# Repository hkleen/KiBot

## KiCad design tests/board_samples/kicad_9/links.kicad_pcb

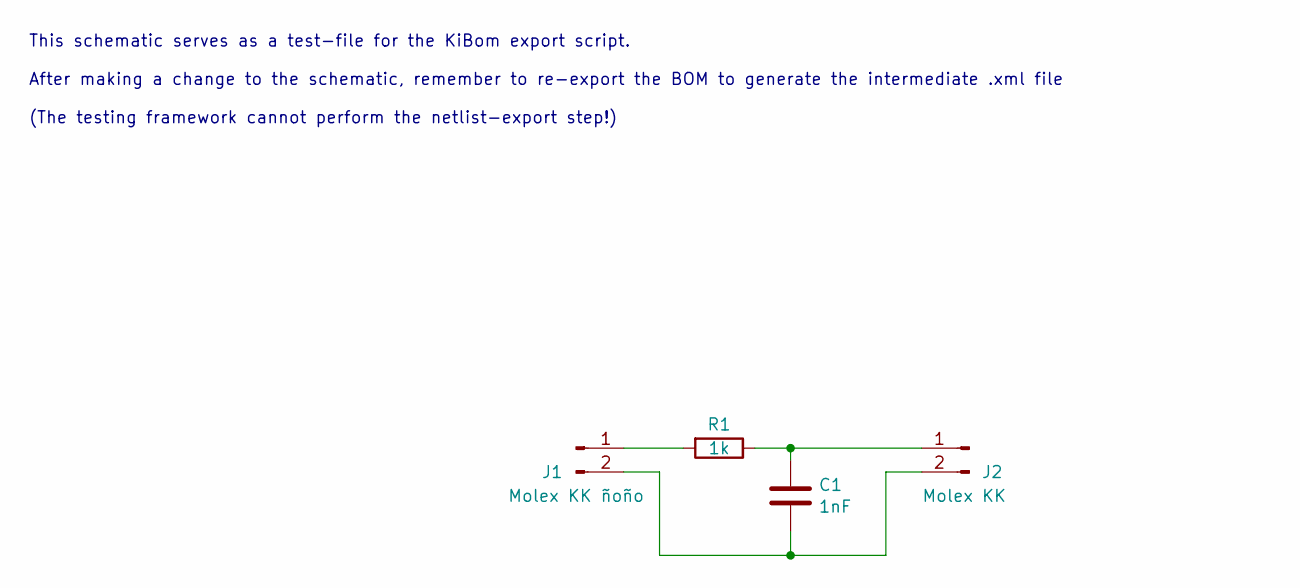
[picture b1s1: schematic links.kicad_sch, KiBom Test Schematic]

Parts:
C1: 1nF; C_0805_2012Metric; mouser# 80-C0805C102K5R; digikey# 399-1147-1-ND
J1: Molex KK ñoño; PinHeader_1x02_P2.54mm_Vertical; mouser# 538-22-23-2021; digikey# 900-0022232021-ND
J2: Molex KK; PinHeader_1x02_P2.54mm_Vertical; mouser# 538-22-23-2021; digikey# 900-0022232021-ND
R1: 1k; R_0805_2012Metric; mouser# 652-CR0805JW-102ELF; digikey# CR0805-JW-102ELFCT-ND

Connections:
unnamed: C1.1, J2.1, R1.1
unnamed: C1.2, J1.2, J2.2
unnamed: J1.1, R1.2

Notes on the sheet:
This schematic serves as a test-file for the KiBom export script. After making a change to the schematic, remember to re-export the BOM to generate the intermediate .xml file (The testing framework cannot perform the netlist-export step!)

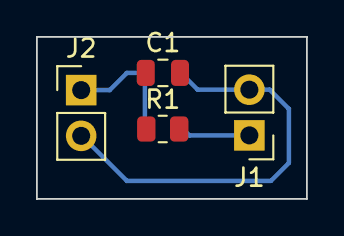
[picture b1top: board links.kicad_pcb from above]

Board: 2 copper layers, 15.0 x 9.0 mm, 4 parts (0 on the bottom side), 3 nets.

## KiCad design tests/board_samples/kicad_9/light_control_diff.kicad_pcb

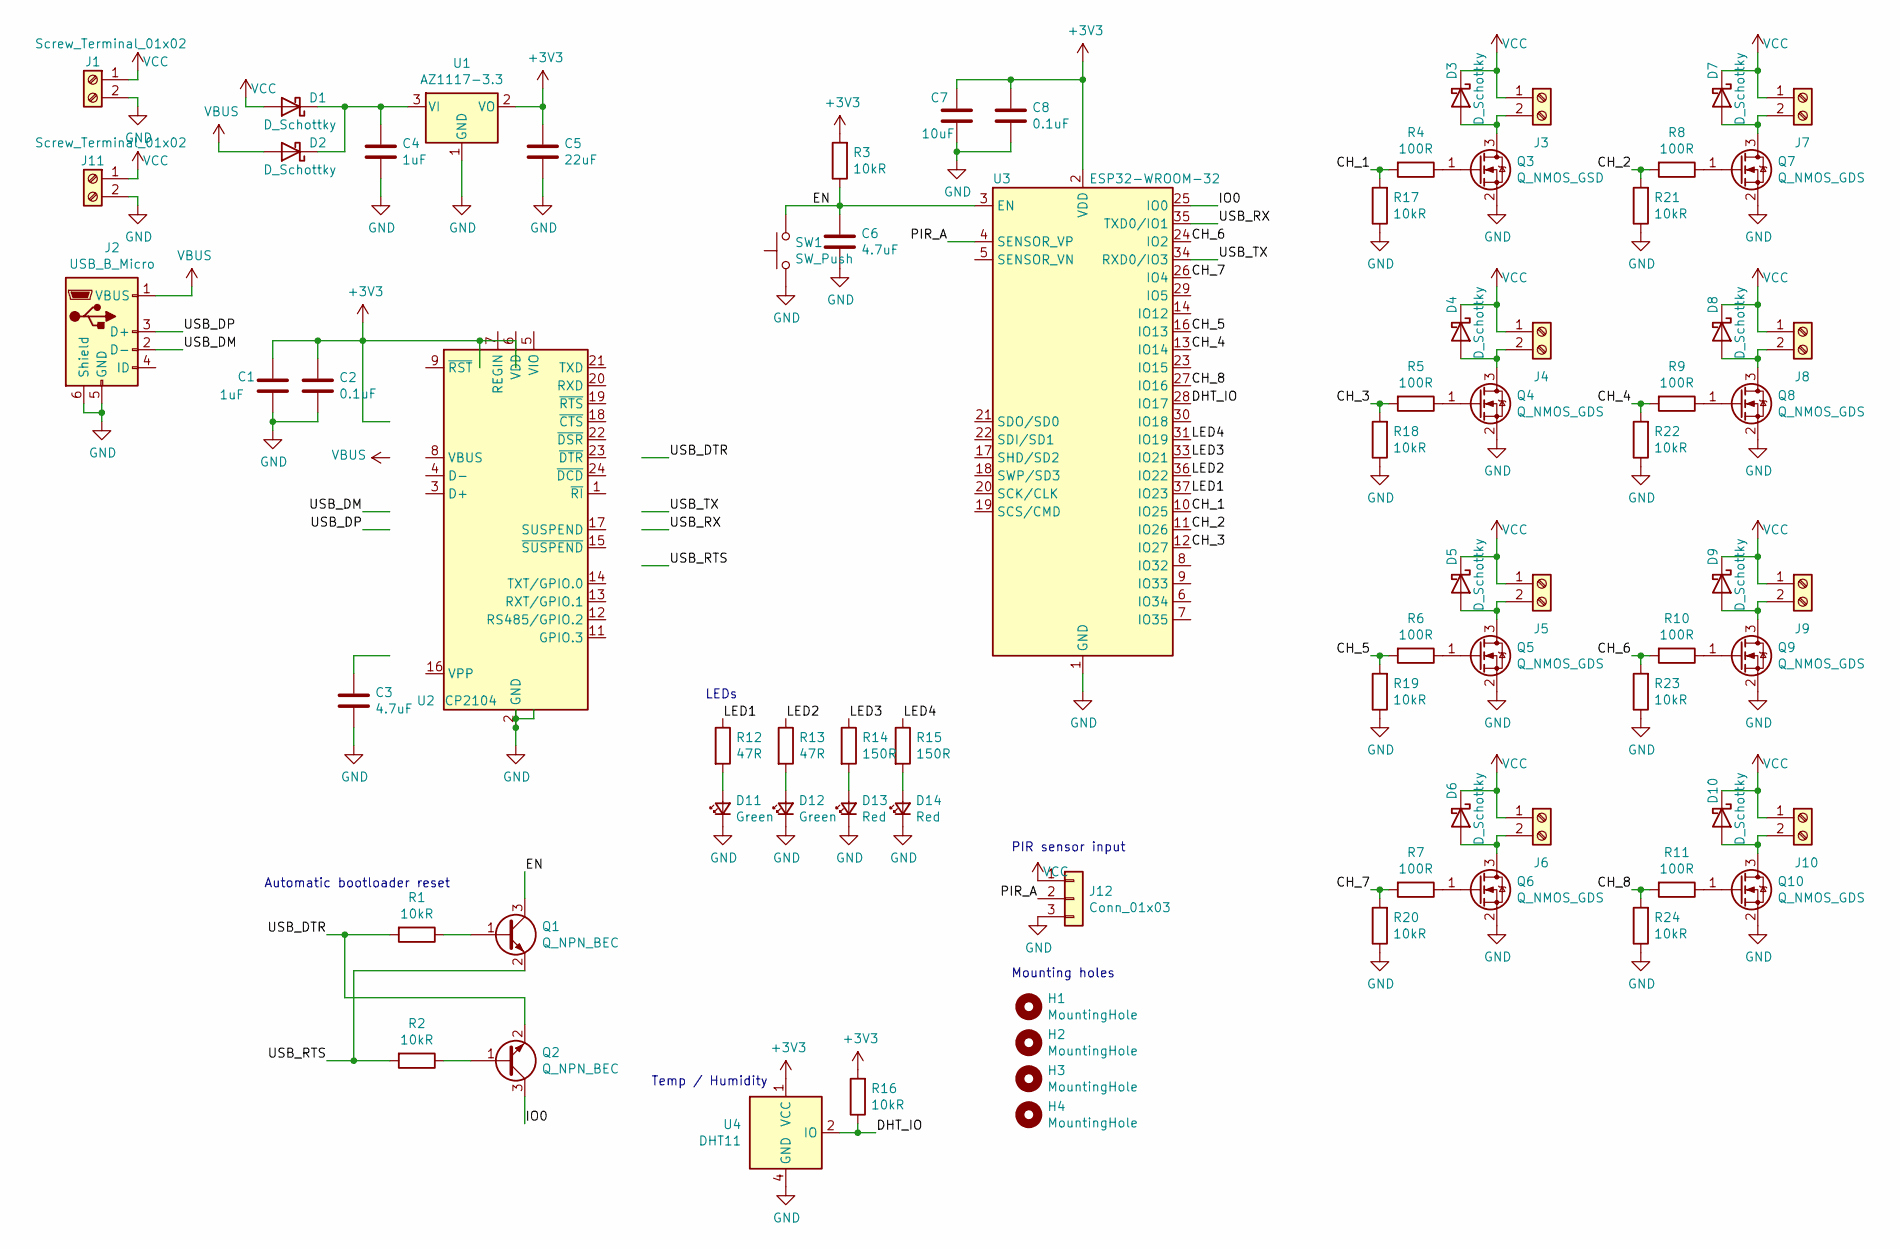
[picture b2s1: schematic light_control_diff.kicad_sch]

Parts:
C1: 1uF; R_0402_1005Metric; MPN CL05A105KA5NQNC; LCSC# C52923
C2, C8: 0.1uF; R_0402_1005Metric; MPN CL05B104KO5NNNC; LCSC# C1525
C3: 4.7uF; R_0603_1608Metric; MPN CL10A475KO8NNNC; LCSC# C19666
C4: 1uF; R_0603_1608Metric; MPN CL10A105KB8NNNC; LCSC# C15849
C5: 22uF; R_0603_1608Metric; MPN CL10A226MQ8NRNC; LCSC# C59461
C6: 4.7uF; R_0402_1005Metric; MPN CL05A475MP5NRNC; LCSC# C23733
C7: 10uF; R_0402_1005Metric; MPN CL05A106MQ5NUNC; LCSC# C15525
D1, D2, D3, D4, D5, D6, D7, D8, D9, D10: D_Schottky; D_SOD-123; MPN B5819W SL; LCSC# C8598
D11, D12: Green; LED_0603_1608Metric; MPN 19-217/GHC-YR1S2/3T; LCSC# C72043
D13, D14: Red; LED_0603_1608Metric; LCSC# C2286
H1, H2, H3, H4: MountingHole; MountingHole_3.2mm_M3
J1, J3, J4, J5, J6, J7, J8, J9, J10, J11: Screw_Terminal_01x02; TerminalBlock_Phoenix_PT-1,5-2-3.5-H_1x02_P3.50mm_Horizontal
J2: USB_B_Micro; USB_Micro-B_Molex-105017-0001
J12: Conn_01x03; JST_XH_B3B-XH-A_1x03_P2.50mm_Vertical
Q1, Q2: Q_NPN_BEC; SOT-23; MPN SS8050; LCSC# C2150
Q3: Q_NMOS_GSD; SOT-23; MPN AO3400A; LCSC# C20917
Q4, Q5, Q6, Q7, Q8, Q9, Q10: Q_NMOS_GDS; SOT-23; MPN AO3400A; LCSC# C20917
R1, R2, R3, R16, R17, R18, R19, R20, R21, R22, R23, R24: 10kR; R_0402_1005Metric; MPN 0402WGF1002TCE; LCSC# C25744
R4, R5, R6, R7, R8, R9, R10, R11: 100R; R_0402_1005Metric; MPN 0402WGF1000TCE; LCSC# C25076
R12: 47R; R_0402_1005Metric; MPN 19-217/GHC-YR1S2/3T; LCSC# C25118
R13: 47R; R_0402_1005Metric; MPN 0402WGF470JTCE; LCSC# C25118
R14, R15: 150R; R_0402_1005Metric; MPN 0402WGF1500TCE; LCSC# C25082
SW1: SW_Push; TS-1187A; MPN TS-1187A-C-D-B; LCSC# C318888
U1: AZ1117-3.3; SOT-223-3_TabPin2; MPN AZ1117CH-3.3TRG1; LCSC# C92102
U2: CP2104; QFN-24-1EP_4x4mm_P0.5mm_EP2.6x2.6mm; MPN CP2104-F03-GMR; LCSC# C47742
U3: ESP32-WROOM-32
U4: DHT11; Aosong_DHT11_5.5x12.0_P2.54mm

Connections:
+3V3: C1.1, C2.1, C5.1, C7.1, C8.1, R3.2, R16.2, U1.2 (VO), U2.5 (VIO), U2.6 (VDD), U2.7 (REGIN), U3.2 (VDD), U4.1 (VCC)
/CH_1: R4.2, R17.2, U3.10 (IO25)
/CH_2: R8.2, R21.2, U3.11 (IO26)
/CH_3: R5.2, R18.2, U3.12 (IO27)
/CH_4: R9.2, R22.2, U3.13 (IO14)
/CH_5: R6.2, R19.2, U3.16 (IO13)
/CH_6: R10.2, R23.2, U3.24 (IO2)
/CH_7: R7.2, R20.2, U3.26 (IO4)
/CH_8: R11.2, R24.2, U3.27 (IO16)
/DHT_IO: R16.1, U3.28 (IO17), U4.2 (IO)
/EN: C6.1, Q1.3 (C), R3.1, SW1.2, U3.3 (EN)
/IO0: Q2.3 (C), U3.25 (IO0)
/LED1: R12.1, U3.37 (IO23)
/LED2: R13.1, U3.36 (IO22)
/LED3: R14.1, U3.33 (IO21)
/LED4: R15.1, U3.31 (IO19)
/PIR_A: J12.2, U3.4 (SENSOR_VP)
/USB_DM: J2.2 (D-), U2.4 (D-)
/USB_DP: J2.3 (D+), U2.3 (D+)
/USB_DTR: Q2.2 (E), R1.2, U2.23 (~DTR)
/USB_RTS: Q1.2 (E), R2.2, U2.19 (~RTS)
/USB_RX: U2.20 (RXD), U3.35 (TXD0/IO1)
/USB_TX: U2.21 (TXD), U3.34 (RXD0/IO3)
GND: C1.2, C2.2, C3.2, C4.2, C5.2, C6.2, C7.2, C8.2, D11.1 (K), D12.1 (K), D13.1 (K), D14.1 (K), J1.2, J2.5 (GND), J2.6 (Shield), J11.2, J12.3, Q3.2 (S), Q4.2 (S), Q5.2 (S), Q6.2 (S), Q7.2 (S), Q8.2 (S), Q9.2 (S), Q10.2 (S), R17.1, R18.1, R19.1, R20.1, R21.1, R22.1, R23.1, R24.1, SW1.1, U1.1 (GND), U2.2 (GND), U2.25 (GND), U3.1 (GND), U3.15 (GND), U3.38 (GND), U3.39 (GND), U4.4 (GND)
unnamed: C3.1, U2.16 (VPP)
unnamed: C4.1, D1.1 (K), D2.1 (K), U1.3 (VI)
unnamed: D3.2 (A), J3.2, Q3.3 (D)
unnamed: D4.2 (A), J4.2, Q4.3 (D)
unnamed: D5.2 (A), J5.2, Q5.3 (D)
unnamed: D6.2 (A), J6.2, Q6.3 (D)
unnamed: D7.2 (A), J7.2, Q7.3 (D)
unnamed: D8.2 (A), J8.2, Q8.3 (D)
unnamed: D9.2 (A), J9.2, Q9.3 (D)
unnamed: D10.2 (A), J10.2, Q10.3 (D)
unnamed: D11.2 (A), R12.2
unnamed: D12.2 (A), R13.2
unnamed: D13.2 (A), R14.2
unnamed: D14.2 (A), R15.2
unnamed: Q1.1 (B), R1.1
unnamed: Q2.1 (B), R2.1
unnamed: Q3.1 (G), R4.1
unnamed: Q4.1 (G), R5.1
unnamed: Q5.1 (G), R6.1
unnamed: Q6.1 (G), R7.1
unnamed: Q7.1 (G), R8.1
unnamed: Q8.1 (G), R9.1
unnamed: Q9.1 (G), R10.1
unnamed: Q10.1 (G), R11.1
VBUS: D2.2 (A), J2.1 (VBUS), U2.8 (VBUS)
VCC: D1.2 (A), D3.1 (K), D4.1 (K), D5.1 (K), D6.1 (K), D7.1 (K), D8.1 (K), D9.1 (K), D10.1 (K), J1.1, J3.1, J4.1, J5.1, J6.1, J7.1, J8.1, J9.1, J10.1, J11.1, J12.1

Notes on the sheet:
PIR sensor input
Mounting holes
Temp / Humidity
LEDs
Automatic bootloader reset

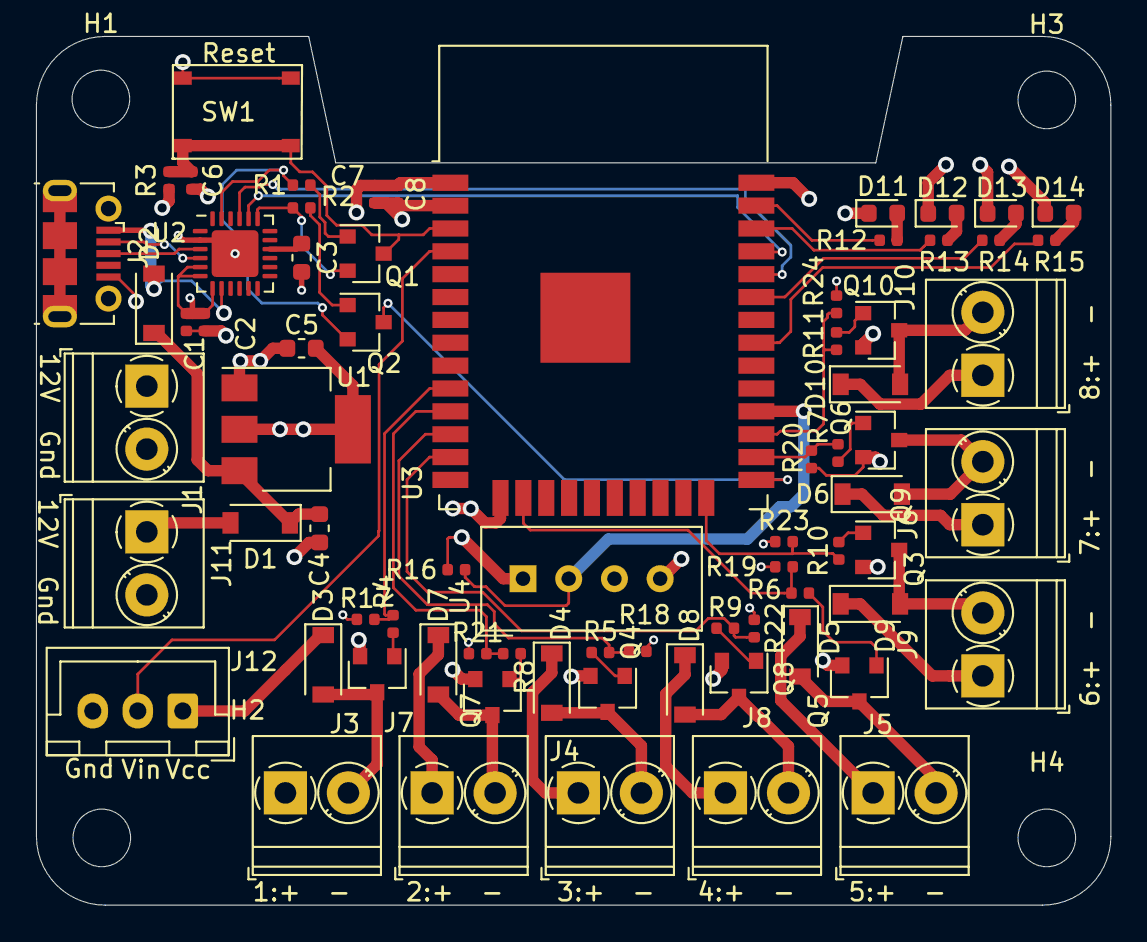
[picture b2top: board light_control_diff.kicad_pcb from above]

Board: 4 copper layers, 59.7 x 48.3 mm, 77 parts (0 on the bottom side), 50 nets.

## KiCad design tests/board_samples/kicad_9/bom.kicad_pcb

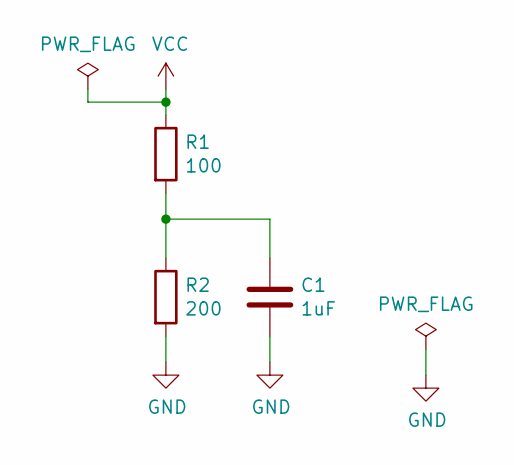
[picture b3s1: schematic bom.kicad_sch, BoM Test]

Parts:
C1: 1uF; C_0805_2012Metric
R1: 100; R_0805_2012Metric
R2: 200; R_0805_2012Metric

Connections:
GND: C1.2, R2.2
unnamed: C1.1, R1.2, R2.1
VCC: R1.1

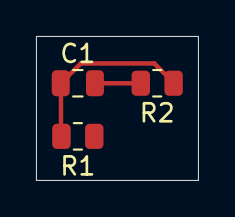
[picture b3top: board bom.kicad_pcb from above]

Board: 2 copper layers, 9.0 x 8.0 mm, 3 parts (0 on the bottom side), 2 nets.

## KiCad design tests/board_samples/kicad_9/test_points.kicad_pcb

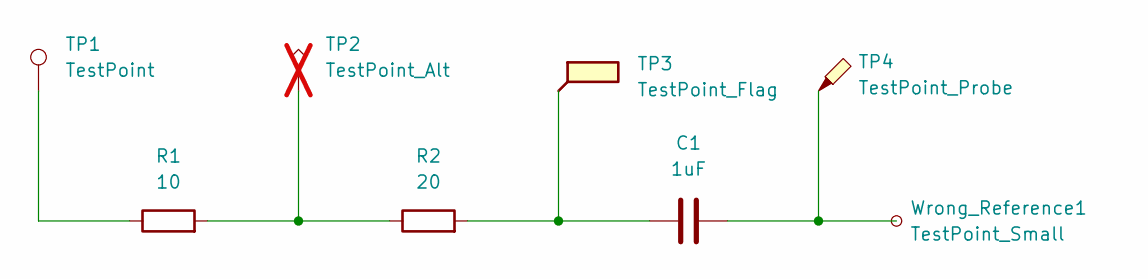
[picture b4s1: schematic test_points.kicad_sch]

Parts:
C1: 1uF; C_0805_2012Metric
R1: 10; R_0805_2012Metric
R2: 20; R_0805_2012Metric
TP1: TestPoint; TestPoint_Loop_D1.80mm_Drill1.0mm_Beaded
TP2: TestPoint_Alt; TestPoint_Pad_1.0x1.0mm; not fitted
TP3: TestPoint_Flag; TestPoint_Plated_Hole_D2.0mm
TP4: TestPoint_Probe; TestPoint_Pad_D2.0mm
Wrong_Reference1: TestPoint_Small; TestPoint_Pad_D1.0mm

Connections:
unnamed: C1.1, R2.2, TP3.1
unnamed: C1.2, TP4.1, Wrong_Reference1.1
unnamed: R1.1, TP1.1
unnamed: R1.2, R2.1, TP2.1

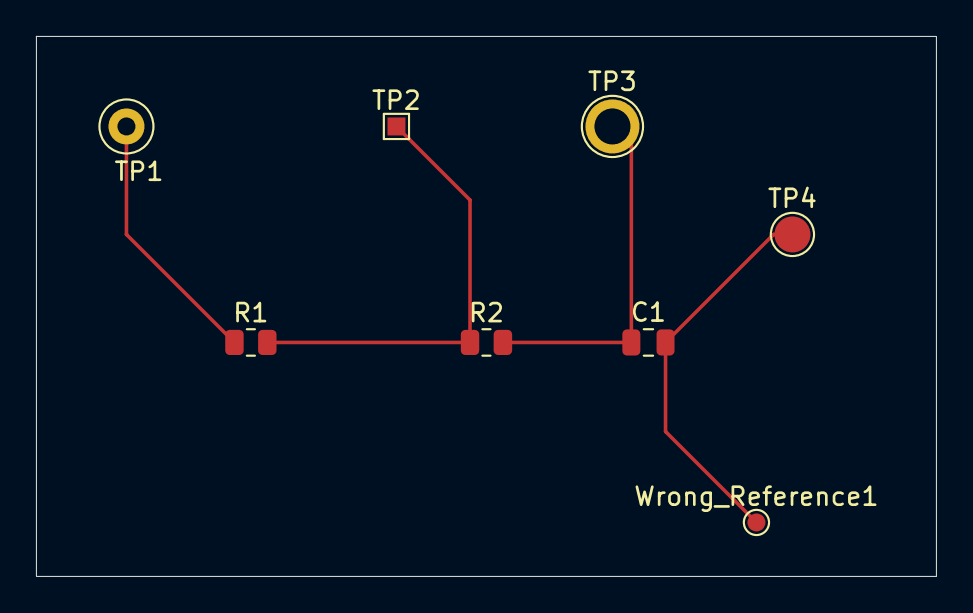
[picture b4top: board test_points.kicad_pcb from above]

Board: 2 copper layers, 50.0 x 30.0 mm, 8 parts (0 on the bottom side), 4 nets.

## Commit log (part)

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2022-03-21 Switched to KiCost/master
2022-04-11 Test to add configurable title block to pcb_print
    - Doesn't work, KiCad can't load the wks from Python, just the default.
2024-05-17 fix indentation
2024-10-29 [PCB Print][Fixed] Problems with the forced edge
    Introduced by the patch that implements #706
2024-10-29 [Debian][Fixed] Missing tools in resources
2024-10-29 [Test][GUI][Preflights] Force to select the dict versions
    When we have boolean + dict
2024-10-30 [BoM][Added] KiCad internal BoM special fields
    At least all the ones I found, trying to make them to behave like in KiCad
2024-10-30 [BoM][Added] Mechanism to import fields from KiCad's BoM
    - You can import the fields and the grouping
    - Also added a new option "group_not_fitted" to mimic KiCad behavior
2024-10-31 [BoM][Added] Range separator configuration
    - `ref_range_separator`
    - Also `use_ref_ranges` alias for `use_alt`
2024-11-01 [PCB Print][Fixed] Groups are KiCad 6+ feature
2024-11-01 [DOCs][BoM][Added] Notes about things not imported from KiCad
    - DNP ex/inclusion, controlled by global `kicad_dnp_applied`
    - String filter, controlled by filters
2024-11-01 [PcbDraw][Changed] SVG size when no contour
    Was 0x0 mm, now is A4 landscape
2024-11-11 Revert "[Changed] Try to use "Rescue" layer again"
    This reverts commit a3e99c178006ccb117bf469e6b556d4d0a483bd2.
2024-11-12 [Fixed] Some times we don't initialize the global options
    So we don't need to check if the global work layer is valid all the time
2024-11-12 [Fixed] The image replacer needs KiCad 6+
    See #713
2024-11-13 [Fix] Handle no matching key for out_to_csv_mapping
2024-11-14 [DOCs][Drill] Updated
    - Also added a warning when generating nothing
    - Also removed redundant option in excellon (from any)
2024-11-14 [Added] Stronger workaround for people using backslashes in WKSs
    Should cover all the cases where we read the WKSs from the project
    See #719 and #607
2024-11-20 [Feature] Support OTF fonts in ressources
2024-11-20 [Preflights][Added][Consolidate_PCBs] To merge PCBs
    This should enable rendering multile PCBs together.
    See #724
2024-11-20 [Fixed] Mal formed -> Malformed
2024-11-20 [iBoM][Fixed] Avoid passing the new filter option to iBoM
2024-11-21 [Subparts Filter][Fixed] 3D ouputs
    See #729
2024-11-21 [Test][GUI] Adjusted the preflight test
    Subparts deprecation
2024-11-21 [Column List][Bom][Added] Added 'Net Label' column
    Similar to Net Name but without the path. Only displays the Net Label given in the schematic
2024-11-22 [Fields][Added] "Net Label" as a valid one
    - Also added it and the other related nets to the ones from KiCad
2024-11-22 [Report][Added][Missing][Template] report_total_components.txt
    See #730
2024-11-28 Config: Panelize: Add missing fiducials plugin options
    Adds `code` and `arg` options to support plugin type for fiducials in
    panelization.
2024-11-28 [Report][Template] Also substract excluded in the components counter
    See #730
2024-11-29 [Tests][Fixed] The new test_int_bom_variant_t4 is for KiCad 8 only
    Uses the new DRC preglight
    See #737
2024-12-05 [BoM][Added] `right_digits` option
    To control the decimals for position fields
    Closes #739
2024-12-16 [Added] Check for PCB to W_MISSFPINFO
    See #741
2024-12-16 fix slicing and index parsing
2024-12-19 [Added] Some profile code for tests
2024-12-20 [Kiri][Added] Pass the debug level to kidiff
    - Trying to figure out fails on GitHub that I can't reproduce locally
2024-12-21 [Report][Fixed] Wrong condition for design settings skip with KiCad 5
2024-12-22 [Fancy Stackup][Added] Option for border thickness
2024-12-22 [Include Table][Removed] unused variable
2024-12-24 [DOCs][Updated] Changelog with the new font mechanism
2024-12-26 [BoM][XLSX][Fixed] Logo size
    To match the old PPIs
    Fixes #750
2024-12-27 [Draw Fancy Stackup][Fixed] Confusing drawing when symmetric vias overlap
    If the bottom layer of the upper via overlaps the top layer of the bottom via
    we can't draw both in the same column
2024-12-27 [Include Table][Fancy Stackup][Fixed] Computation of font width
2024-12-30 [Draw Fancy Stackup][Changed] Micro vias drawing
    To look closer to real world, they only span 2 layers and they
    must be stacked to span more layers.
2024-12-30 [DOCs][Added] New Include table option (force_font_width)
    See #752
2025-01-02 [Definitions][Fixed] Empty definition handling
    Avoid interpreting them as the "None" string, now they are just None
    See #757
2025-01-02 [Drill Tests][Removed] Do not specify default PTH/NPTH IDs
2025-01-03 [Any Layer][KiCad 9] Tent vias no longer used
    Now you set it for each via
2025-01-03 [KiCad 9] No more LAYER_HIDDEN_TEXT
    Lets hope its side effect also went away ...
2025-01-03 [KiCad 9][Added] Support for the new BOX2I constructor
2025-01-03 [KiCad 9][Layer] More adjusts for the new layer numbering
2025-01-03 [Drill Info][Added] support for KiCad 9 new layer numbering
2025-01-03 [Drill Info/Tests] Fix tests for Ki5
    PAD_ATTRIB_NPTH was not available and 3Rs_bv not consistent with other versions
2025-01-03 [Drill Info][Fixed] Layer numbering for KiCad 9
2025-01-03 [Any Drill][Removed] unused debug log
2025-01-06 [Any Drill][Modified] To make more explicit the columns added by KiCad 6+
2025-01-06 [Tests][Any Drill][Added] For some errors in the table spec
2025-01-06 [Tests][GUI][Any Drill] Adapted to the new table option
2025-01-06 [DOCs][Added] Notes about using booleans in definitions
    Also a warning for complex data types
    See #762
2025-01-07 [PCB Print][Added] Drill Map drawing
2025-01-07 [KiCad 9] No longer raises an exception on PCB failed load
2025-01-07 [PCB Print][KiCad 9] More tent vias fixes
2025-01-07 [Include Table][Fixed] wrong group_suffix with index
2025-01-07 [PCB Print][Fixed] handle empty table param
2025-01-07 [Include Table] Use a set for VALID_DRILL_TABLE_OUTPUTS
2025-01-07 [PCB Print Tests][Fixed] Also include V9+ in drillmap tests
2025-01-08 [KiCad 9][Added] Note about pcbnew.BOX2I constructor
    Looks like the old version is available again
2025-01-09 [Drill Marks][Fixed] draw_oval
    - The way to compare the angles
    - A workaround for ANGLE +=/-= free() issue
2025-01-09 [PcbDraw][KiCad 9][Added] Support
    Basically is like KiCad 8
2025-01-10 [Tests][DRC][KiCad 9] Added support for the new messages
2025-01-10 [PCB Print][KiCad 9][Fixed] Copper layer detection
2025-01-10 [PCB Print][Fixed] drill map needs KiCad 7 or newer
2025-01-10 [DOCs][PCB Print][Fixed] %lnp -> %lpn
2025-01-10 [Drill Info][Changed] Now layer pairs are sorted
    - To make it more repeatable
    - KiCad 9 seems to sort vias this way
2025-01-13 [YAML Examples][Added] Farnell costs test
2025-01-13 [YAML Examples][Added] QR Lib with one dict
    The other example is a list of dict
2025-01-13 [YAML Examples][Added] Export project
2025-01-13 [YAML Examples][Added] Fancy Draw Stack-up example
2025-01-13 [Info][Added] Whitepaper that helps to understand microvias issues
2025-01-14 [KiCad 9] Workaround for bug 19546
    Hope it gets solved
2025-01-18 [Nav Res Modern][Changed] Various changes
    Icon and text layout in the top menu
    Clickable paths for arbitrary ancestors
    Up arrow to go back in history
    Arbitrary logo size
    Atomic inclusion of markdown-it.js
2025-01-18 [Navigate Results Modern][Fixed] Underindentation
2025-01-18 [Nav Res Modern][Fixed] Disable transition on page load
    For the search bar to avoid flickering
2025-01-18 [BaseOutput][Added] note about root path for category
2025-01-18 [Nav Res Modern][Removed] Duplicate code for search bar
2025-01-18 [Any Navigate Results][Removed] Unused imports
2025-01-20 [Tests][Reference][Updated] KiCad 8.0.8
    Another one
2025-01-21 [Tests][Navigate Results] Adapted to the RB version
2025-01-27 [Navigate Results][Fixed] Not variantic
2025-01-27 [Tests][GUI][Added] Missing navigate_results_rb
2025-02-04 [Check Fields][Added] Mechanism to check for extra fields
    Closes #774
2025-02-05 [PCB Print][Fixed] Layer handling issues
    - Wrong sketch_pads_on_fab_layers default value introduce by
    6c352691192d1a41ef715ad8992215b5a605f36c
    - sketch_pads_on_fab_layers not inherited from parent when using
    layer names
    - Some layer options (use_for_center, sketch_pads_on_fab_layers and
    exclude_filter) not copied on repeated layers
2025-02-05 Avoid extra warnings for PCB fields with spaces
    See #778
2025-02-11 [Tests] Disable KiCad 9 deprecation warning
2025-02-11 [Drill][KiCad 9] Adapted the Ln-Lm layer numbers
2025-02-11 [Tests][KiCad 9][Added] Test file
2025-02-14 [Schematic][Added][KiCad 9] Support for new hide style in pin_names
2025-02-14 [Blender Export][Added] option to avoid soldering heatsinks
2025-02-17 [CI/CD][Added] Experimental KiCad 9 (nightly) tests
2025-02-17 [CI/CD][Blender] Try to install at system level
    GitHub runs the docker image as root, but changes the HOME so root
    settings are lost
2025-02-17 [CI/CD][Tests] Enabling all tests
2025-02-19 [CI/CD] Fixed dev images OS tag
    - Is currently Debian stable
2025-02-19 [Datasheet download] Bumped user agent
    No real need, just a refresh for testing
2025-02-20 [Dependencies] Allow to specify a different version for KiCad versions
    Applied to KiKit
2025-02-20 [Dependency Downloader][Fixed] Version extraction
2025-02-20 [DOCs] Updated KiKit deps, needs more work
2025-02-21 [KiBot Checker][Added] Correct version check for KiKit
    - According to KiCad version
    - Also allow KiCad 9
2025-02-24 [CI/CD][Tests] Changed to KiCad 9 release
2025-02-24 [CI/CD][Dev Images] Changing to KiCad 9 release
2025-02-25 [Navigate Results] Avoid centering the markdown text
2025-02-25 [Added][Example] Report with markdown
    To test the navigate results
2025-02-25 [CI/CD][Dev Images][Fixed] No need to install curl
    As we are currently using kicad/kicad images for KiCad 9
2025-02-25 [ODB][Fixed] Debug messages
2025-02-26 [Added][IPC2581] New output to generate IPC-DPMX files
2025-02-26 [Added][Export 3D] New output using KiCad 9 CLI
    - Replaces STEP
    - Adds STL, glTF binary, XAO and BRep support
2025-02-28 [Fixed] Typo in comment
2025-03-05 [CI/CD] Updating Github Action v2 for KiCad 9 development
2025-03-10 [Schematic][KiCad 9][Added] Bezier curves at top level
2025-03-10 [Tests][Fixed] Schematic references for KiCad >= 6
    Bezier indentation change
2025-03-14 [BoM][Added] New sort style: field
    - To sort by one or more arbitrary fields.
    - `sort_field` option to specify the field/s.
2025-03-18 [DOCs] Updated version info for release
2025-03-18 [CI/CD][Release][Added] KiCad 9 triggers
2025-03-18 [Debian][Added] Missing 1.8.2-2 release
2025-03-19 [KiCad 9][Added] Support for multiple sizes in one via
    - For reports we take the smaller ring
    - In the print so we restore the sizes properly
2025-03-20 [BoM][Added] New column "Footprint Full"
    To get the LIB:NAME
2025-03-20 [BoM][Added] `kicad_dnp_applied` to overwrite the global one
2025-03-26 [Tests][Fixed][KiCad 9] Annotate reference
    Moved embedded fonts
2025-03-27 [DOCs][Added] KiCad 9 docker tags
2025-04-01 [Added] Support for embedded worksheets
2025-04-01 [PCB Print][Fixed] Case when no layout is specified
2025-04-03 [Tests][References] Schematic print for KiCad 9.0.1
    Net classes and sheet paths changes colors
2025-04-03 [Tests][Reference] Adjusts fot 9.0.1
    Fonts are rendered differently on SVGs, difference in the border
2025-04-22 [Makefile] KiCad 9 as default
2025-04-24 [Fixed][KiCad 9] User.N layer numbering
    Fixes #808
2025-05-06 [Schematic][Added] Support for private fields
    Closes #812
2025-05-06 [Tests][Updated] test_v5.kicad_sch reference
    Change in "pp" field visibility
2025-05-07 [3D][Added] SHA256 hash for replaced models
    - Only for debug > 2
    See #804
